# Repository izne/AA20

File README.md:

# AA20

A compact, high-fidelity audio amplifier PCB centered around the legendary TDA2003. 

## The Spirit of the TDA2003

There is something undeniably cool about the TDA2003. It packs a full Class B transistor amplifier into a single, robust package—a feat of engineering that remains a cornerstone of analog audio. While it belongs to an "old-school" era of design, it delivers that unmistakable, warm, and punchy transistor sound that modern digital chips often struggle to replicate. It's simple, it's powerful, and it's pure analog soul.

### Engineering Facts
The TDA2003 is a monolithic audio power amplifier IC designed as a low-frequency **Class B amplifier**. By utilizing a push-pull configuration, it achieves high power efficiency while maintaining low harmonic distortion. It is engineered for stability and reliability, featuring:
- **Monolithic Design:** Integrates the entire power amplifier circuit into a single chip.
- **High Power Output:** Capable of delivering significant power (typically 10W+) depending on the configuration.
- **Robust Protection:** Built-in features to handle typical operating stresses, making it a favorite for car audio and home stereo applications.

## Overview

AA20 is designed to be a small but mighty amplifier solution. The layout is specifically optimized for thermal performance, mounting the TDA2003 ICs sideways to facilitate efficient side-mounted heatsinking.

## Schematic & Design Philosophy

The circuit design is a direct implementation of the **TDA2003 reference schematic** provided in the official datasheet. To ensure maximum reliability and performance, all component values (capacitors, resistors, and diodes) are selected strictly according to the manufacturer's recommendations. 

This approach guarantees that the amplifier operates within its intended stability margins, providing the expected output power and low distortion while effectively managing the Zobel network for high-frequency stability.

## Performance Analysis (Theoretical)

Based on a **12V DC** supply and an **8 $\Omega$** load, the following performance characteristics are expected:

### Power Output
Using the relationship $P = \frac{V_{peak}^2}{2R}$, and accounting for the typical $V_{drop}$ of the TDA2003:
- **Estimated Output Power:** $\approx$ **2.5W to 3.5W per channel** at peak levels.
- **Current Draw:** With a 12V 2A supply, the system has ample headroom to drive both channels even under heavy transients.

### Thermal & Efficiency
- **Efficiency:** As a Class B amplifier, it offers higher efficiency than Class A, reducing wasted energy.
- **Heat Dissipation:** At peak output, each channel will dissipate significant heat. The side-mounted heatsink configuration is critical to maintaining junction temperatures within safe limits.

### Audio Fidelity
- **Total Harmonic Distortion (THD):** Expected to be **< 0.1%** at rated power, providing clean, high-fidelity audio.
- **Frequency Response:** Designed to cover the full audible spectrum (**20Hz to 20kHz**) with a flat response, thanks to the optimized Zobel network.

## Technical Specifications

### PCB Design
- **General Traces:** 1.5mm width for robust power and high-current paths.
- **Signal Traces:** Precision 0.5mm width for clean audio signal paths.
- **Zobel Network:** 0.5mm trace width for critical stability components.
- **EDA Tool:** KiCad

### Electrical & Load
- **Integrated Circuit:** TDA2003
- **Power Supply:** 12V 2A single power brick (shared across both channels).
- **Speaker Load:** 8 $\Omega$ (15W speakers).

## Visuals

| Schematic | Bottom View |
| :---: | :---: |
|  |  |

## Hardware Notes

- **Thermal Management:** The TDA2003 components are oriented sideways. **A dedicated heatsink must be mounted to the side of the ICs** to ensure stable operation and prevent thermal shutdown.
- **Assembly:** Follow the datasheet reference schematic closely, particularly for the Zobel network placement, to ensure maximum stability and prevent oscillation.

## Files

- `Signal/`: KiCad project files (`.kicad_pro`, `.kicad_sch`, `.kicad_pcb`).
- `Gerbers/Signal/`: Production-ready Gerber files (`rev3.zip`).

## License

[Specify License, e.g., MIT]

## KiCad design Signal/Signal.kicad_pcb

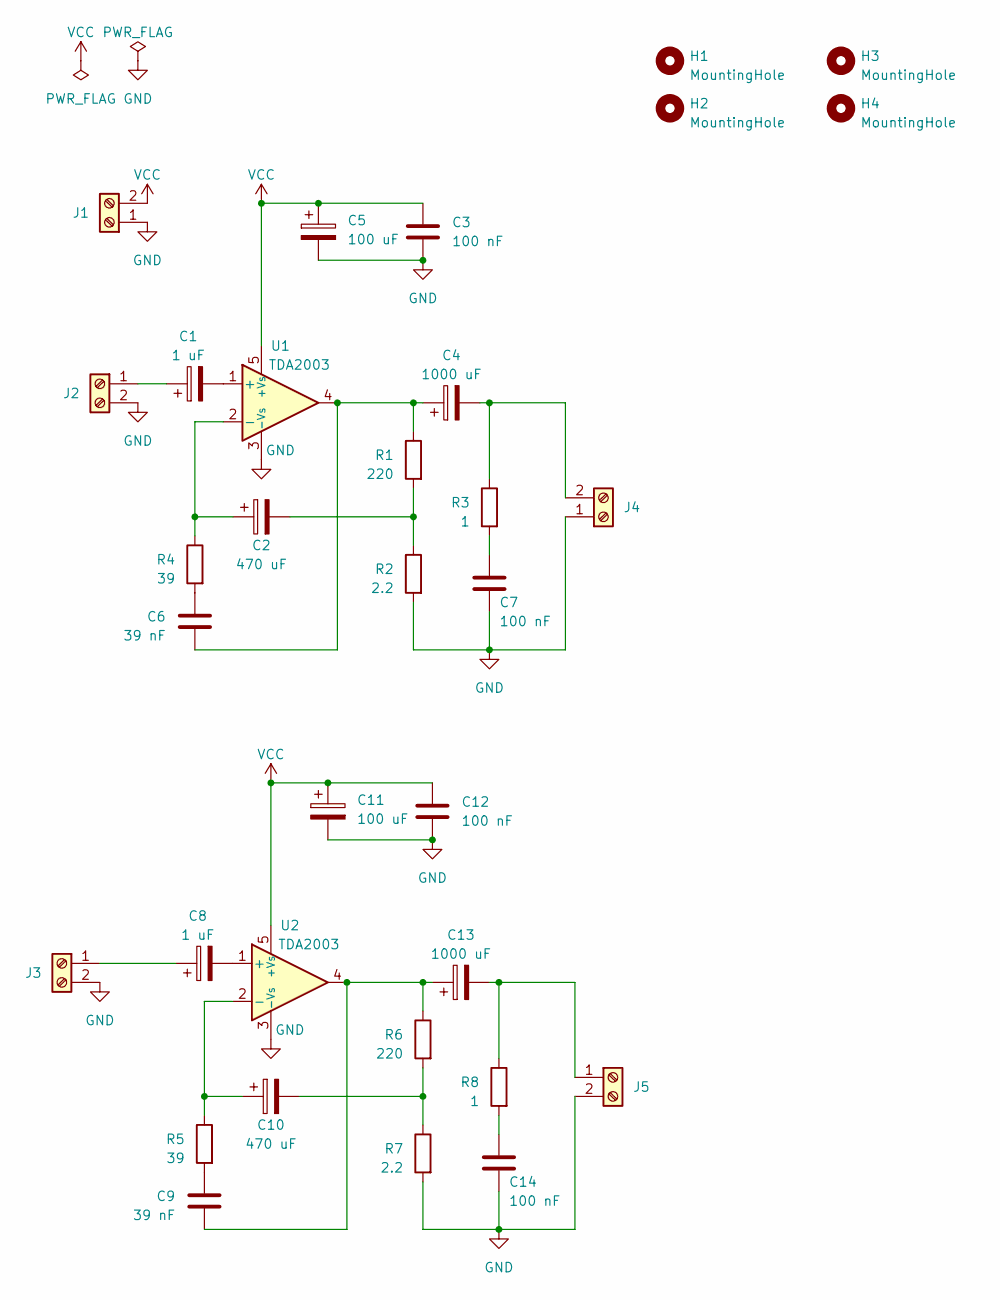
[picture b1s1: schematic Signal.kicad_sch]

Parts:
C1, C8: 1 uF; C_Axial_L19.0mm_D8.0mm_P25.00mm_Horizontal
C2, C10: 470 uF; CP_Radial_D8.0mm_P2.50mm
C3, C12: 100 nF; C_Rect_L4.6mm_W2.0mm_P2.50mm_MKS02_FKP02
C4, C13: 1000 uF; CP_Radial_D12.5mm_P5.00mm
C5, C11: 100 uF; CP_Radial_D6.3mm_P2.50mm
C6, C9: 39 nF; C_Disc_D5.0mm_W2.5mm_P2.50mm
C7, C14: 100 nF; C_Disc_D5.0mm_W2.5mm_P2.50mm
H1, H2, H3, H4: MountingHole; MountingHole_3.2mm_M3
J1, J2, J3, J4, J5: Screw_Terminal_01x02; TerminalBlock_Phoenix_PT-1,5-2-3.5-H_1x02_P3.50mm_Horizontal
R1, R6: 220; R_Axial_DIN0204_L3.6mm_D1.6mm_P2.54mm_Vertical
R2, R7: 2.2; R_Axial_DIN0204_L3.6mm_D1.6mm_P2.54mm_Vertical
R3, R8: 1; R_Axial_DIN0204_L3.6mm_D1.6mm_P2.54mm_Vertical
R4, R5: 39; R_Axial_DIN0204_L3.6mm_D1.6mm_P2.54mm_Vertical
U1, U2: TDA2003; TO-220-5_P3.4x3.7mm_StaggerOdd_Lead3.8mm_Vertical

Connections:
GND: C3.2, C5.2, C7.2, C11.2, C12.2, C14.2, J1.1, J2.2, J3.2, J4.1, J5.2, R2.2, R7.2, U1.3 (-Vs), U2.3 (-Vs)
unnamed: C2.2, R1.2, R2.1
unnamed: C4.1, C6.2, R1.1, U1.4
unnamed: C6.1, R4.2
unnamed: C7.1, R3.2
unnamed: C9.1, R5.2
unnamed: C10.2, R6.2, R7.1
unnamed: C9.2, C13.1, R6.1, U2.4
unnamed: C14.1, R8.2
unnamed: C1.1, J2.1
unnamed: C8.1, J3.1
unnamed: C4.2, J4.2, R3.1
unnamed: C13.2, J5.1, R8.1
unnamed: C1.2, U1.1 (+)
unnamed: C2.1, R4.1, U1.2 (-)
unnamed: C8.2, U2.1 (+)
unnamed: C10.1, R5.1, U2.2 (-)
VCC: C3.1, C5.1, C11.1, C12.1, J1.2, U1.5 (+Vs), U2.5 (+Vs)

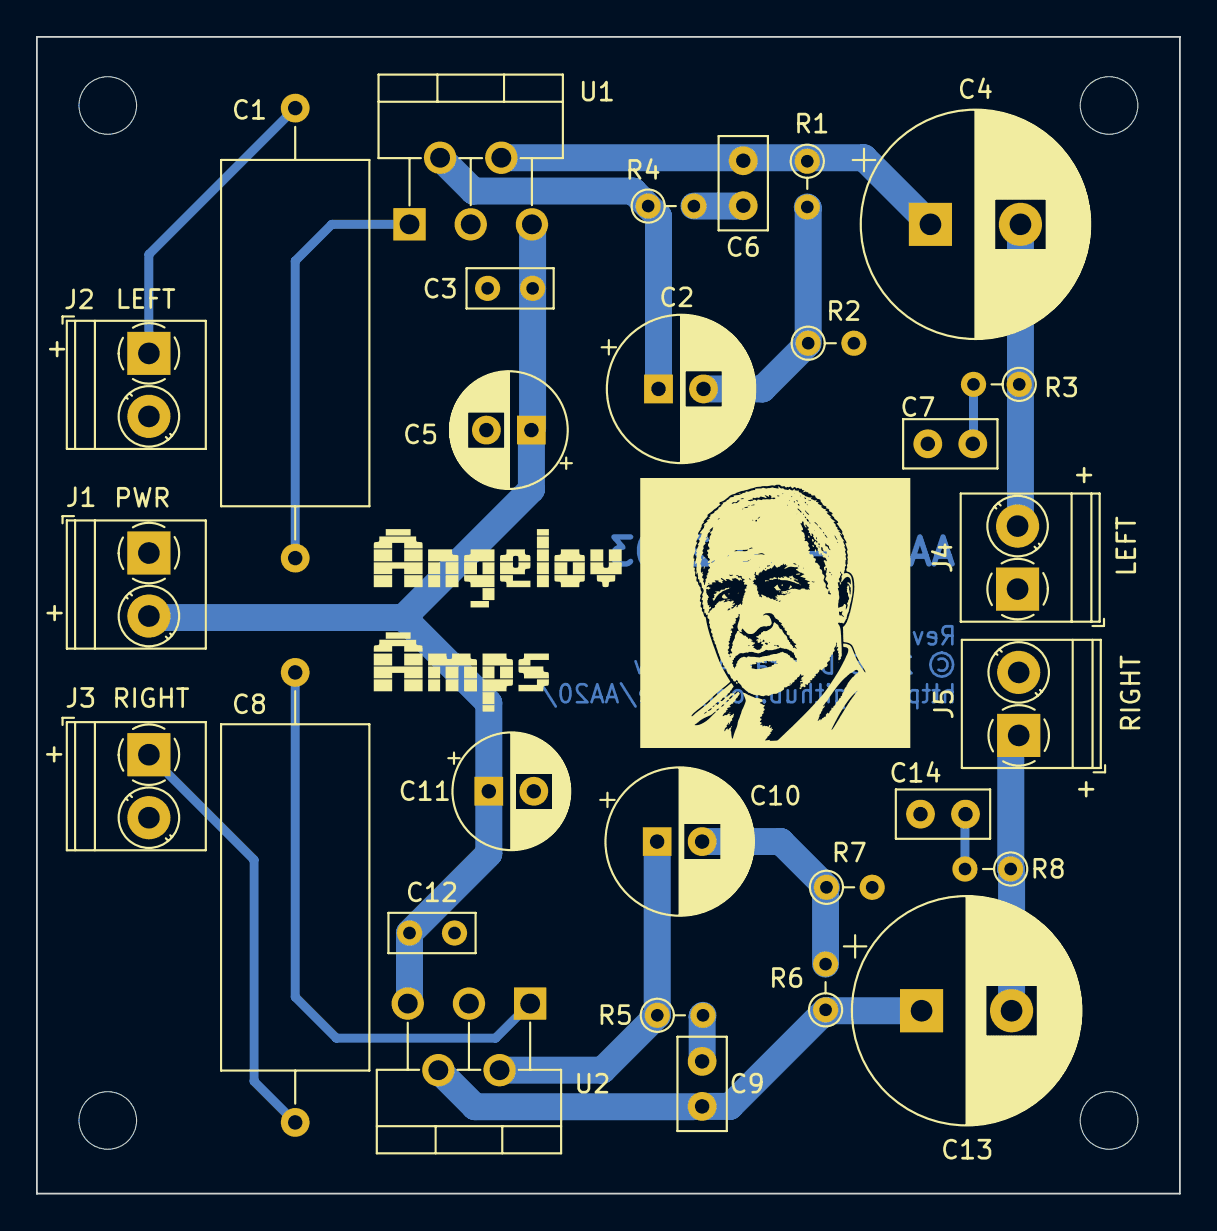
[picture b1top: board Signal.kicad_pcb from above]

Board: 2 copper layers, 63.5 x 64.3 mm, 33 parts (0 on the bottom side), 18 nets.

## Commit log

2026-04-27 First commit. Revision 3 Signal and Gerbers.
2026-04-27 Docs update
2026-04-27 Pics

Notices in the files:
Signal/Signal.kicad_pcb:
© 2026 Dimitar Angelov
